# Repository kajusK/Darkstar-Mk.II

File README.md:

DarkStar Mk.II
==============

Small lightweight, water/mud/shock/bomb proof headlamp with bat roasting
light output and Scurion like body for 1/8 of the price. If you are caver,
mine explorer, biker, etc. with hacker soul, this is a way to go!

Features
--------
* Two high power high efficiency XP-L2 LEDs and two low power (e.g. red + UV).
* Up to 869 ANSI lumens (with 80 CRI 4000 K LEDs).
* Anodized aluminium alloy body.
* 3D printed battery box.
* Waterproof up to 2 (tested) meters (IPx8).
* 2 meter drop resistance tested
* Works in wide temperature range - minus 20 °C to plus 60 °C
* Custom high efficiency LED drivers - up to 96 %.
* Up to 2 Amps per LED.
* Runs on single Li-Ion cell, two are recommended for higher run times.
* Thoroughly tested - see [Measurements](./Measurements.md) for more details.
* Simple API for writing custom user modes.
* Temperature and voltage limits to avoid sudden power off or overheating.
* Long run time (over 30 days on lowest mode, over 1,5 hour on full power - for two 3400 mAh cells).
* Low power off current (27 uA), no need to unplug battery after use.
* Easily replaceable LEDs.
* Weights only 277 grams with two 18650 cells.
* Automated light control based on amount of reflected light (EXPERIMENTAL).
* Custom li-ion protection circuit - up to 7 Amps.

Weight
------
* Lamp: 92 g
* Battery box: 50 g
* 2x18650 battery pack: 97 g
* Head strap: 38 g

HowTo
=====
Directories
-----------
* **avr** Source code and hex files for AVR
* **pcb** circuit diagrams, PCBs, gerber files and BOM for electrical parts
* **mechanical** Mechanical BOM, drawings, STLs

Electronics
-----------
The LED drivers were custom designed from elementary components, no integrated
LED solution was used. It's based on hystersis driven buck converter with current
feedback.

The current is sensed by 0,056 ohm resistor, voltage across this resistor is
amplified by opamp and fed to the comparator. The comparator is a brain of the
driver. When the measured voltage is higher than reference voltage generated by
MCU, comparator turns the MOSFET off, current drops below hystersis, MOSFET is turned on
and the cycle repeats. Nothing fancy, but quite simple and cheap.
Only few parts are required and measured efficiency is reaching 96 %. Over 90 \% for
currents over 0,5 A for whole supply voltage range allowed.
Check [Measurement](./Measurements.md) for more details.
The maximal current allowed is 2 Amps. It should be possible to get much higher
currents by choosing better (bigger and more expensice) inductors and transistors.

Disadvantage of such design is a limited lowest possible current, it can't go
below half of the hystersis current. For this reason 10-100 % output is constant
current driven, 0-10 % is controlled by additional PWM.

Software
--------

The brain of the lamp is Attiny 841, it handles key presses, reference voltage
generating, etc. To make it simpler to program I use optiboot arduino compatible
bootloader though there is no arduino code included in the project except
the bootloader itself.

To make it simpler to write your own control modes, most of the code is just a library
controlling the hardware and providing few quite low level functions to user. It
takes care of reading buttons, generating reference voltages for LED drivers, etc.

It also contains automated light control (PI regulator). The light is measured
by phototransistor and the difference between the measured value and value
required is run through the PI regulator. Result is the applied to reference
voltage generator. This feature is quite EXPERIMENTAL and doesn't work
well for caving when the lamps gets covered in mud.

The rest is the user mode. Check [simple mode](./avr/src/modes/simple.c) to see
how simple it can get. All relevant header are included. See [HowTo](./HowTo.md)
for more details on programming and stuff.

The caving mode controls are described in [User guide](./User_guide.md).

Mechanical
----------
The body is machined on a lathe from 6063 aluminium alloy. No fancy expensive
tools except lathe and drill press are required to make the lamp.

Top cover is made from polycarbonate sheet, cable and control rods bushings are
made from brass. The whole thing is sealed with O-rings. See the [BOM](./mechanical/BOM.md)
for more details.

The battery box is designed to be printed on any 3D printer. I would suggest
using ABS and painting the resulting print with ABS juice to get is as
waterproof as possible.

Lenses
------
the wide beam led can be used without lenses, the beam is wide enough for my
needs, for the narrow beam led you can buy any compatible lens that fits inside
the body. I used [17mm 10deg lens]
(http://www.aliexpress.com/item/free-shipping-cree-xp-g-lens-diameter-17mm-smooth-surface-with-stand-condenser-lenses-10-deg/777222733.html)

License
=======

The source code is licenced under [GNU GPL v2](./avr/LICENSE). The mechanical and
electrical design is licensed under [CERN OHL v.1.2](LICENSE).

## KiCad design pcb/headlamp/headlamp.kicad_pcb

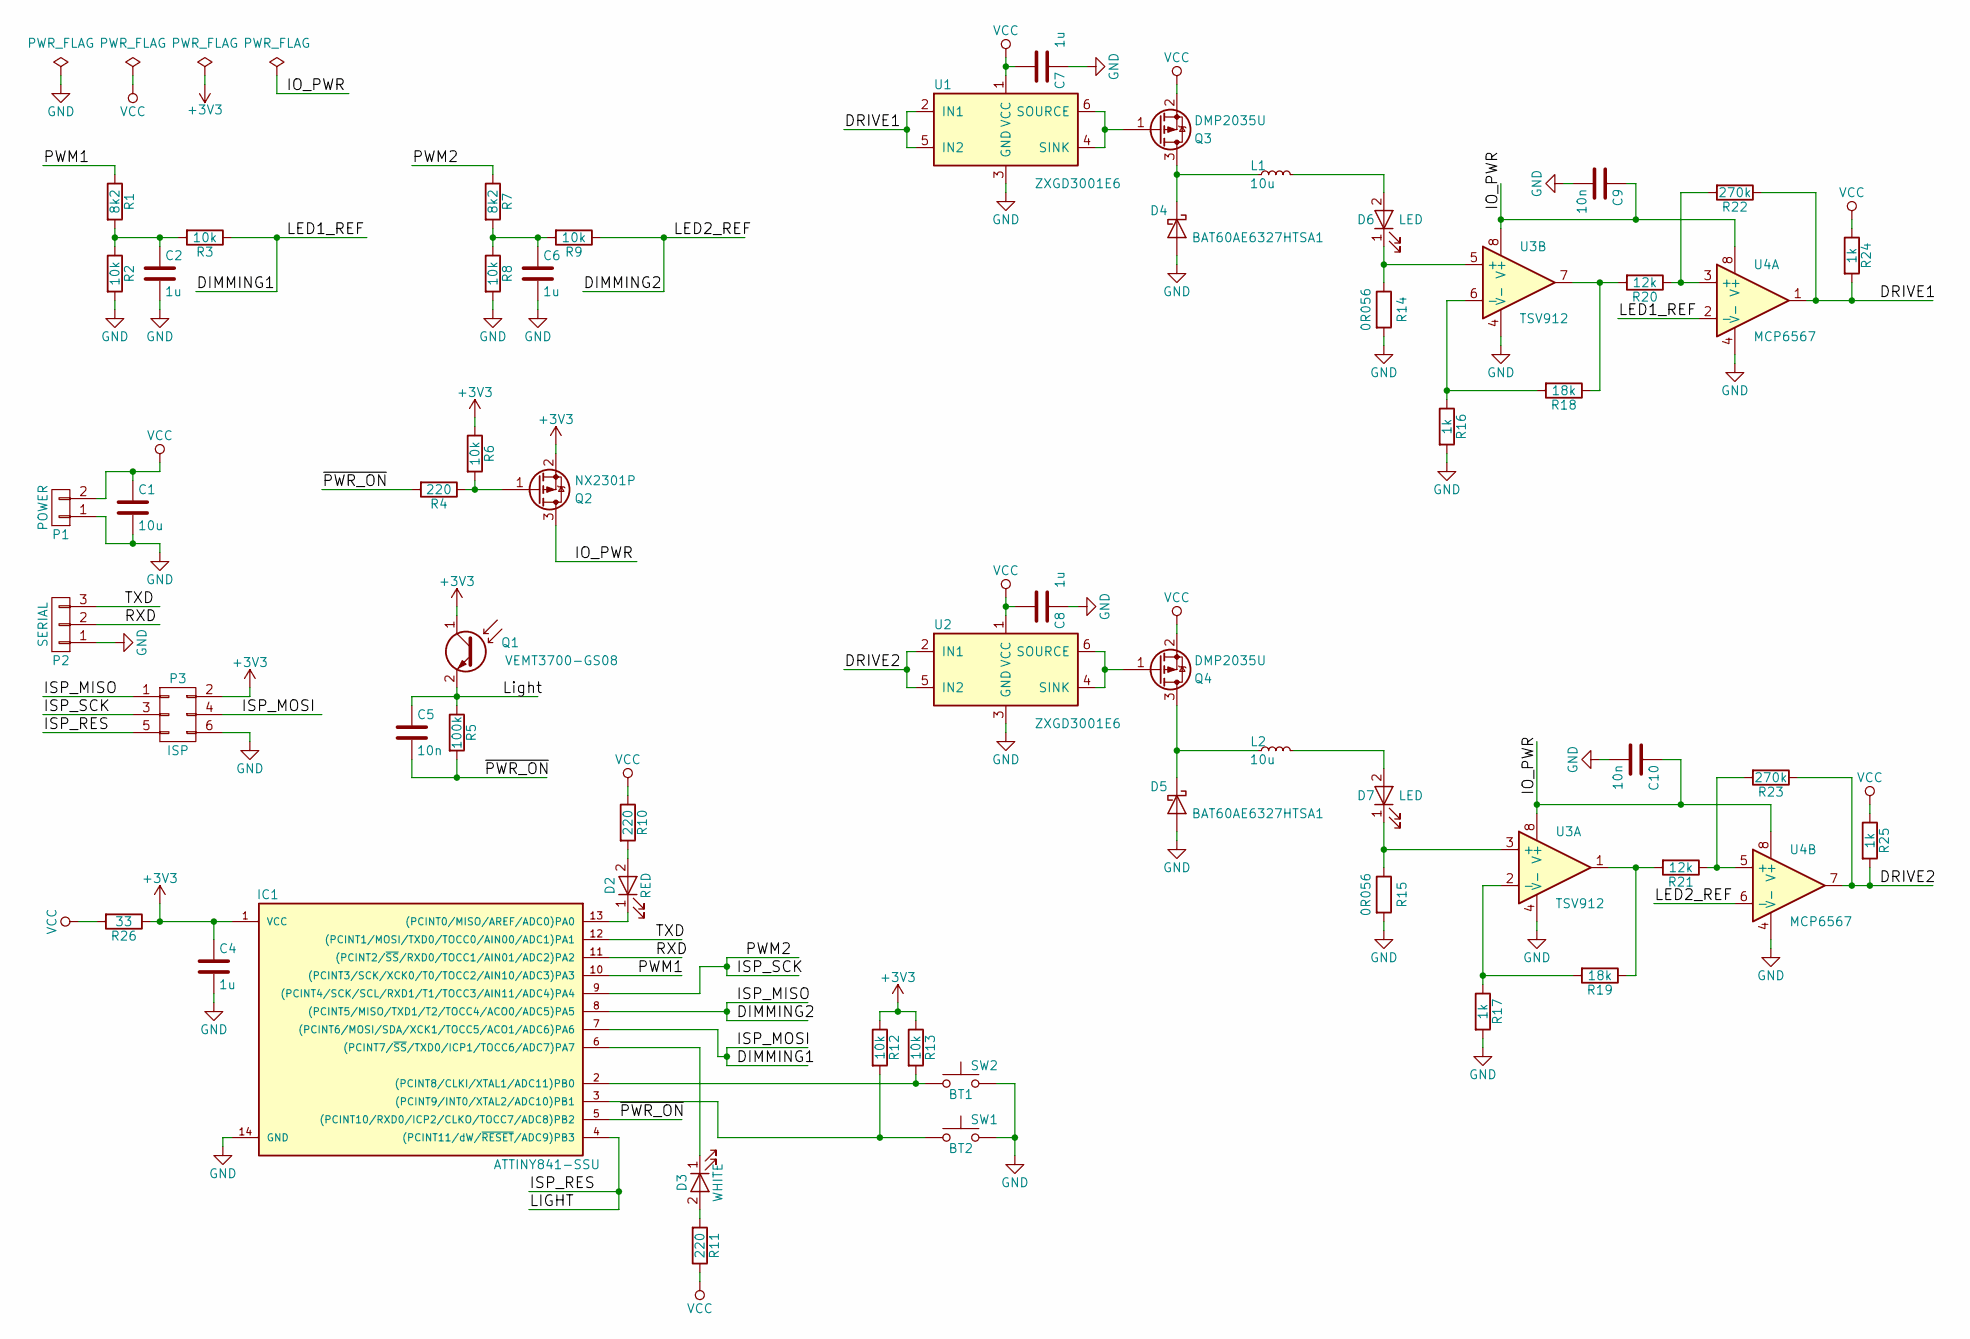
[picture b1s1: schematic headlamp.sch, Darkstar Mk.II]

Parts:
C1: 10u; C_0603
C2, C4, C6, C7, C8: 1u; C_0603
C5, C9, C10: 10n; C_0603
D2: RED; LED_PLCC-2
D3: WHITE; LED_PLCC-2
D4, D5: BAT60AE6327HTSA1; SOD-323
D6, D7: LED; Custom_Conn_2_Big
IC1: ATTINY841-SSU; SOIC-14_3.9x8.7mm_Pitch1.27mm
L1, L2: 10u; Inductor_Bourns-SRU8043
P1: POWER; Custom_Conn_2_Big
P2: SERIAL; GS3
P3: ISP; SOT-23-6
Q1: VEMT3700-GS08; LED_PLCC-2
Q2: NX2301P; SOT-23
Q3, Q4: DMP2035U; SOT-23
R1, R7: 8k2; R_0603
R2, R3, R6, R8, R9, R12, R13: 10k; R_0603
R4, R10, R11: 220; R_0603
R5: 100k; R_0603
R14, R15: 0R056; R_1206
R16, R17, R24, R25: 1k; R_0603
R18, R19: 18k; R_0603
R20, R21: 12k; R_0603
R22, R23: 270k; R_0603
R26: 33; R_0603
SW1: BT2; SW_SPST_FSMSM
SW2: BT1; SW_SPST_FSMSM
U1, U2: ZXGD3001E6; SOT-23-6
U3: TSV912; MSOP-8_3x3mm_Pitch0.65mm
U4: MCP6567; MSOP-8_3x3mm_Pitch0.65mm

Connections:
+3V3: C4.1, IC1.1 (VCC), P3.2, Q1.1 (C), Q2.2 (S), R6.1, R12.1, R13.1, R26.1
/DIMMING1: IC1.7 ((PCINT6/MOSI/SDA/XCK1/TOCC5/ACO1/ADC6)P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), P3.4, R3.1, U4.2 (-)
/DIMMING2: IC1.8 ((PCINT5/MISO/TXD1/T2/TOCC4/ACO0/ADC5)PA5), P3.1, R9.1, U4.6 (-)
/DRIVE1: R22.1, R24.2, U1.2 (IN1), U1.5 (IN2), U4.1
/DRIVE2: R23.1, R25.2, U2.2 (IN1), U2.5 (IN2), U4.7
/IO_PWR: C9.1, C10.1, Q2.3 (D), U3.8 (V+), U4.8 (V+)
/ISP_RES: C5.1, IC1.4 ((PCINT11/dW/~RESET~/ADC9)PB3), P3.5, Q1.2 (E), R5.1
/ISP_SCK: IC1.9 ((PCINT4/SCK/SCL/RXD1/T1/TOCC3/AIN11/ADC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), P3.3, R7.1
/PWM1: IC1.10 ((PCINT3/SCK/XCK0/T0/TOCC2/AIN10/ADC3)PA3), R1.1
/RXD: IC1.11 ((PCINT2/~SS~/RXD0/TOCC1/AIN01/ADC2)PA2), P2.2
/TXD: IC1.12 ((PCINT1/MOSI/TXD0/TOCC0/AIN00/ADC1)PA1), P2.3
/~PWR_ON: C5.2, IC1.5 ((PCINT10/RXD0/ICP2/CLKO/TOCC7/ADC8)PB2), R4.2, R5.2
GND: C1.2, C2.2, C4.2, C6.2, C7.1, C8.1, C9.2, C10.2, D4.2 (A), D5.2 (A), IC1.14 (GND), P1.1, P2.1, P3.6, R2.2, R8.2, R14.2, R15.2, R16.2, R17.2, SW1.2, SW2.2, U1.3 (GND), U2.3 (GND), U3.4 (V-), U4.4 (V-)
unnamed: C2.1, R1.2, R2.1, R3.2
unnamed: C6.1, R7.2, R8.1, R9.2
unnamed: D2.1 (K), IC1.13 ((PCINT0/MISO/AREF/ADC0)PA0)
unnamed: D2.2 (A), R10.2
unnamed: D3.1 (K), IC1.6 ((PCINT7/~SS~/TXD0/ICP1/TOCC6/ADC7)PA7)
unnamed: D3.2 (A), R11.2
unnamed: D4.1 (K), L1.1, Q3.3 (D)
unnamed: D5.1 (K), L2.1, Q4.3 (D)
unnamed: D6.1 (K), R14.1, U3.5 (+)
unnamed: D6.2 (A), L1.2
unnamed: D7.1 (K), R15.1, U3.3 (+)
unnamed: D7.2 (A), L2.2
unnamed: IC1.2 ((PCINT8/CLKI/XTAL1/ADC11)PB0), R13.2, SW2.1
unnamed: IC1.3 ((PCINT9/INT0/XTAL2/ADC10)PB1), R12.2, SW1.1
unnamed: Q2.1 (G), R4.1, R6.2
unnamed: Q3.1 (G), U1.4 (SINK), U1.6 (SOURCE)
unnamed: Q4.1 (G), U2.4 (SINK), U2.6 (SOURCE)
unnamed: R16.1, R18.2, U3.6 (-)
unnamed: R17.1, R19.2, U3.2 (-)
unnamed: R18.1, R20.2, U3.7
unnamed: R19.1, R21.2, U3.1
unnamed: R20.1, R22.2, U4.3 (+)
unnamed: R21.1, R23.2, U4.5 (+)
VCC: C1.1, C7.2, C8.2, P1.2, Q3.2 (S), Q4.2 (S), R10.1, R11.1, R24.1, R25.1, R26.2, U1.1 (VCC), U2.1 (VCC)

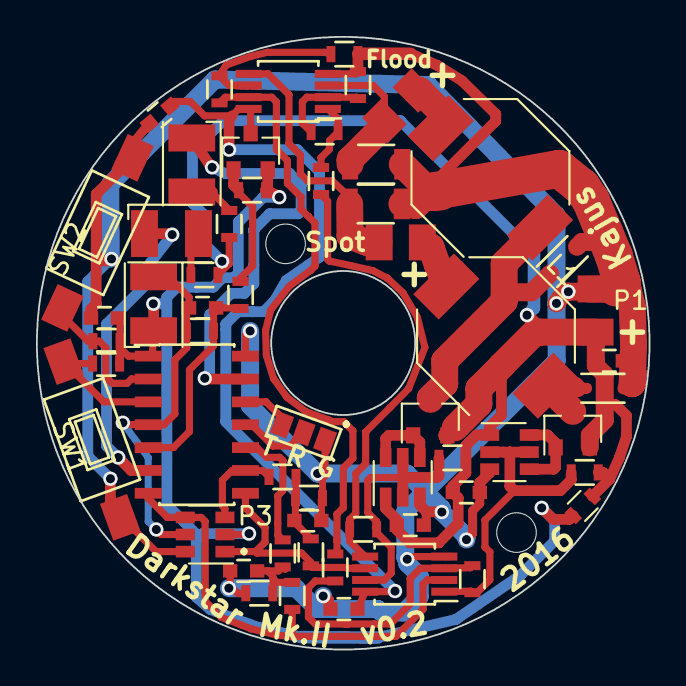
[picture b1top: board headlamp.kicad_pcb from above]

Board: 2 copper layers, 34.0 x 34.0 mm, 57 parts (0 on the bottom side), 37 nets.

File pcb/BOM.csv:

Reference, Value, Footprint,URL
C1,10u,Capacitors_SMD:C_0603,
C10,10n,Capacitors_SMD:C_0603,
C2,1u,Capacitors_SMD:C_0603,
C4,1u,Capacitors_SMD:C_0603,
C5,10n,Capacitors_SMD:C_0603,
C6,1u,Capacitors_SMD:C_0603,
C7,1u,Capacitors_SMD:C_0603,
C8,1u,Capacitors_SMD:C_0603,
C9,10n,Capacitors_SMD:C_0603,
D2,RED,LEDs:LED_PLCC-2,http://cz.farnell.com/osram/lr-t67f-u1aa-1/led-smd-plcc2-red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
D3,WHITE,LEDs:LED_PLCC-2,http://cz.farnell.com/broadcom-limited/asmt-uwb1-nx3e2/led-s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
D4,BAT60AE6327HTSA1,Diodes_SMD:SOD-323,http://cz.farnell.com/infineon/bat-60a-e6327/rectifier-schot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
D5,BAT60AE6327HTSA1,Diodes_SMD:SOD-323,http://cz.farnell.com/infineon/bat-60a-e6327/rectifier-schot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
D6,CREE XP-L2,,http://cz.mouser.com/ProductDetail/Cree-Inc/XPLBWT-00-0000-0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
D7,CREE XP-L2,,http://cz.mouser.com/ProductDetail/Cree-Inc/XPLBWT-00-0000-0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
IC1,ATTINY841-SSU,Housings_SOIC:SOIC-14_3.9x8.7mm_Pitch1.27mm,http://cz.farnell.com/atmel/attiny841-ssur/mcu-8bit-attiny-1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
L1,10u,Inductors:Inductor_Bourns-SRU8043,http://cz.farnell.com/bourns/sru8043-100y/choke-power-shield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
L2,10u,Inductors:Inductor_Bourns-SRU8043,http://cz.farnell.com/bourns/sru8043-100y/choke-power-shield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
Q1,VEMT3700-GS08,LEDs:LED_PLCC-2,http://cz.farnell.com/vishay/vemt3700-gs08/photo-transistor-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
Q2,NX2301P,TO_SOT_Packages_SMD:SOT-23,http://cz.farnell.com/nxp/nx2301p/mosfet-p-ch-20v-2a-sot23/d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
Q3,DMP2035U,TO_SOT_Packages_SMD:SOT-23,http://cz.farnell.com/diodes-inc/dmp2035u/mosfet-p-ch-esd-20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
Q4,DMP2035U,TO_SOT_Packages_SMD:SOT-23,http://cz.farnell.com/diodes-inc/dmp2035u/mosfet-p-ch-esd-20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
R1,8k2,Resistors_SMD:R_0603,
R10,220R,Resistors_SMD:R_0603,
R11,220R,Resistors_SMD:R_0603,
R12,10k,Resistors_SMD:R_0603,
R13,10k,Resistors_SMD:R_0603,
R14,0R056,Resistors_SMD:R_1206,http://cz.farnell.com/te-connectivity/rlp73n2br056jtd/resist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
R15,0R056,Resistors_SMD:R_1206,http://cz.farnell.com/te-connectivity/rlp73n2br056jtd/resist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
R16,1k,Resistors_SMD:R_0603,
R17,1k,Resistors_SMD:R_0603,
R18,18k,Resistors_SMD:R_0603,
R19,18k,Resistors_SMD:R_0603,
R2,10k,Resistors_SMD:R_0603,
R20,12k,Resistors_SMD:R_0603,
R21,12k,Resistors_SMD:R_0603,
R22,270k,Resistors_SMD:R_0603,
R23,270k,Resistors_SMD:R_0603,
R24,1k,Resistors_SMD:R_0603,
R25,1k,Resistors_SMD:R_0603,
R26,33R,Resistors_SMD:R_0603,
R3,10k,Resistors_SMD:R_0603,
R4,220R,Resistors_SMD:R_0603,
R5,10k,Resistors_SMD:R_0603,
R6,10k,Resistors_SMD:R_0603,
R7,8k2,Resistors_SMD:R_0603,
R8,10k,Resistors_SMD:R_0603,
R9,10k,Resistors_SMD:R_0603,
SW1,BT2,Buttons_Switches_SMD:SW_SPST_FSMSM,http://cz.farnell.com/alcoswitch-te-connectivity/1437566-3/p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
SW2,BT1,Buttons_Switches_SMD:SW_SPST_FSMSM,http://cz.farnell.com/alcoswitch-te-connectivity/1437566-3/p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
U1,ZXGD3001E6,TO_SOT_Packages_SMD:SOT-23-6,http://cz.farnell.com/diodes-inc/zxgd3001e6ta/driver-gate-bi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
U2,ZXGD3001E6,TO_SOT_Packages_SMD:SOT-23-6,http://cz.farnell.com/diodes-inc/zxgd3001e6ta/driver-gate-bi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
U3,TSV912,Housings_SSOP:MSOP-8_3x3mm_Pitch0.65mm,http://cz.farnell.com/stmicroelectronics/tsv912aiyst/op-amp-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
U4,MCP6567,Housings_SSOP:MSOP-8_3x3mm_Pitch0.65mm,http://cz.farnell.com/microchip/mcp6567-e-ms/ic-comparator-d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

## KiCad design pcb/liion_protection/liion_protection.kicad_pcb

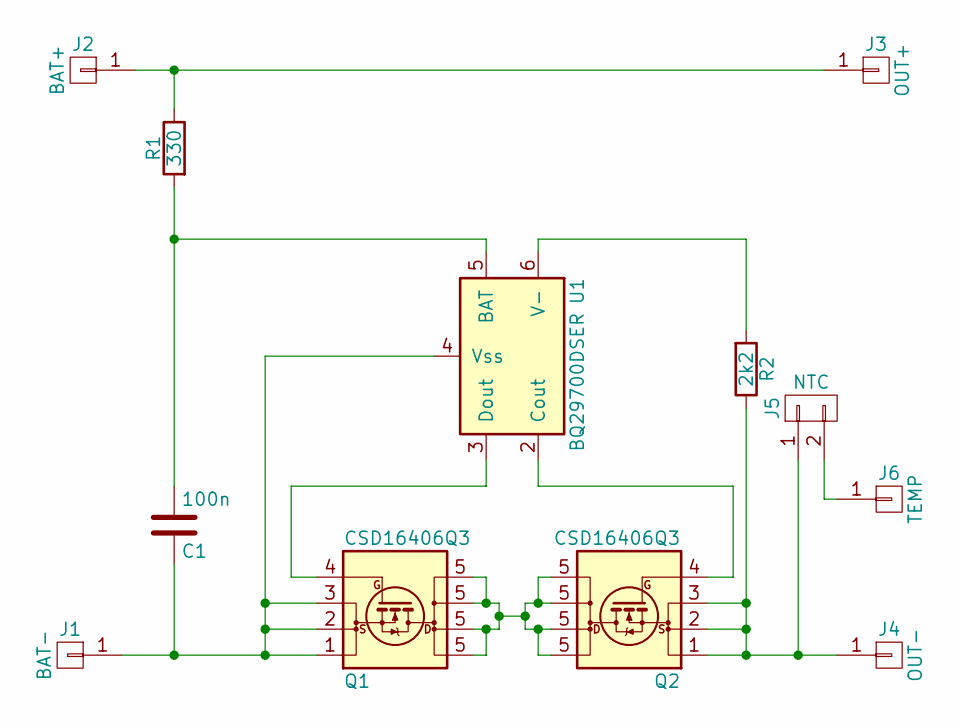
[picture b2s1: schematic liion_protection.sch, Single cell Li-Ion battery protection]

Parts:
C1: 100n; C_0603
J1: BAT-; 1Pin
J2: BAT+; 1Pin
J3: OUT+; 1Pin
J4: OUT-; 1Pin
J5: NTC; GS2
J6: TEMP; 1Pin
Q1, Q2: CSD16406Q3; VSON-8_3.3x3.3mm_Pitch0.65mm_NexFET
R1: 330; R_0603
R2: 2k2; R_0603
U1: BQ29700DSER; WSON6_1.5x1.5mm_Pitch0.5mm

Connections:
unnamed: C1.1, J1.1, Q1.1 (S), Q1.2 (S), Q1.3 (S), U1.4 (Vss)
unnamed: C1.2, R1.2, U1.5 (BAT)
unnamed: J2.1, J3.1, R1.1
unnamed: J4.1, J5.1, Q2.1 (S), Q2.2 (S), Q2.3 (S), R2.1
unnamed: J5.2, J6.1
unnamed: Q1.4 (G), U1.3 (Dout)
unnamed: Q1.5 (D), Q2.5 (D)
unnamed: Q2.4 (G), U1.2 (Cout)
unnamed: R2.2, U1.6 (V-)

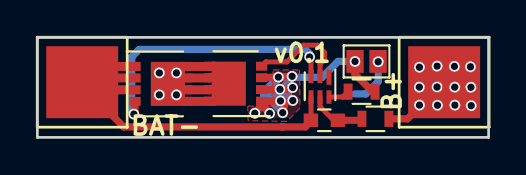
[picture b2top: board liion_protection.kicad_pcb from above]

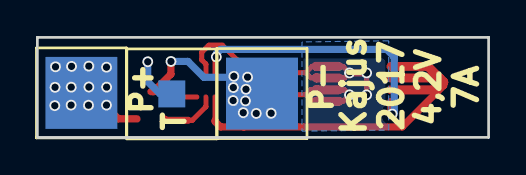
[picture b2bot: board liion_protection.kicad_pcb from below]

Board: 2 copper layers, 25.1 x 5.6 mm, 12 parts (3 on the bottom side), 9 nets.

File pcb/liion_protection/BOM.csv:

Reference, Value, Footprint,URL
Q2,CSD16406Q3,Housings_SON:VSON-8_3.3x3.3mm_Pitch0.65mm_NexFET,http://cz.mouser.com/search/ProductDetail.aspx?R=0virtualkey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
Q1,CSD16406Q3,Housings_SON:VSON-8_3.3x3.3mm_Pitch0.65mm_NexFET,http://cz.mouser.com/search/ProductDetail.aspx?R=0virtualkey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
R2,2k2,Resistors_SMD:R_0603,
R1,330R,Resistors_SMD:R_0603,
C1,100n,Capacitors_SMD:C_0603,
U1,BQ29700DSER,Housings_SON:WSON6_1.5x1.5mm_Pitch0.5mm,http://cz.mouser.com/search/ProductDetail.aspx?R=0virtualkey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

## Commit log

2016-12-04 Rearranged schematics
2016-12-10 Switched to open drain comparator
2016-12-19 First draft of source code
2016-12-20 Added led driver code
2016-12-20 Fixed missing dependency
2016-12-20 Added led pwm dimming
2016-12-20 Fixed typo
2016-12-20 License added
2016-12-20 Simple system timer added
2016-12-20 LEDs moved to hal layer
2016-12-22 Added button handling
2016-12-22 Buttons reading added
2016-12-22 Power off added
2016-12-23 Added forgotten wdt timeout
2016-12-23 PWM dimming must be slower
2016-12-23 Updated function naming
2016-12-23 Events timing added
2016-12-23 Determine amount of ram left
2016-12-28 Board added
2016-12-31 Added gerber files
2016-12-31 Added leds_enabled check function
2016-12-31 Disable leds when going to sleep
2016-12-31 ADC voltage returned in mV
2017-01-01 Added light management
2017-01-01 Main loop added
2017-01-01 Updated makefile to allow compiling different headlamp modes
2017-01-03 Renamed and cleaned sleep function
2017-01-03 Added support for dropin on in supply rail diode protection aka peak detector
2017-01-03 Interrupts setting
2017-01-03 Added power off handling
2017-01-03 Fixed button detection
2017-01-03 added light off function
2017-01-03 Added simple control mode
2017-01-12 Added system_loop function
2017-01-12 removed trailing whitespace
2017-01-12 Added wake up from multiple sources
2017-01-13 Added millis to system library
2017-01-23 Fixed binary safe uart
2017-01-29 Fixed small LEDs connections
2017-01-29 Fixed PWM incorrect register setting
2017-01-29 Fixed typos
2017-01-29 Updated port mapping to match board
2017-01-29 Fixed ram_free declaration
2017-01-29 Fixed =/== error
2017-01-29 Final schematic values, pcb
2017-01-29 Fixed millis timing, attiny not setting overflow flag on match overflow
2017-01-29 Fixed blinking
2017-01-30 Moved get_state to inline
2017-01-30 Turn off pwm output when brightness == 0
2017-01-30 leds enable/disable simplified
2017-01-30 Fixed simple mode light settings
2017-02-03 Fixed uart
2017-02-03 Fixed adc pin setting and conversion result
2017-02-03 ADCL must be read before ADCH
2017-02-03 Updated calculation of vcc for higher accuracy
2017-02-03 Reduced adc frequency for improved accuracy
2017-02-03 Updated defines for adc api
2017-02-03 fixed system voltage reading when diode is used
2017-02-03 Fixed limits clear
2017-02-03 Fixed programming speed
2017-02-03 Updated system constants
2017-02-03 Turn off pwm when battery dead or body overheated
2017-02-11 Added hystersis to limits
2017-02-11 Ignore limits for small leds
2017-02-11 Slowed dimming PWM - the output was not stable over 150Hz
2017-02-16 Updated low voltage levels
2017-03-06 Added user limits
2017-03-06 Hard limits updated
2017-03-09 added option to disable uart
2017-03-09 Added config read/write for storing user data to eeprom
2017-03-09 Added logging wdt resets to eeprom
2017-03-09 Cleaned main
2017-03-09 Added button press detection after powerup
2017-03-09 Fixed initial value of eeprom wdt reset counter
2017-03-09 Caving mode draft
2017-03-09 Fixed hole between short and long press
2017-03-09 Initialize mode in init rather than in variable definition
2017-03-10 Refractored simple mode
2017-03-11 Fixed PWM settings for led
2017-03-11 Updated capacitors values
2017-03-11 Simple mode for hardware testing
2017-03-11 Fixed waking up
2017-03-11 fixed modes switching in simple mode
2017-03-11 fixed level switching
2017-03-17 Fixed button reading on startup
2017-03-17 Minor fixes to caving mode
2017-03-18 Updated phototransistor wiring due to error on board
2017-03-19 Added pid light regulation
2017-03-19 added WDT reset after waking up
2017-03-20 Updated default blink level to reasonable value
2017-03-20 Added config mode
2017-03-20 Removed unnecessary output settings for blinking
2017-03-21 Updated config read/write definition
2017-03-21 Output hex has same name as the mode
2017-03-21 Read temperature and voltage only once per cycle
2017-03-21 Auto mode can't be used together with dimming
2017-03-21 Updated selftest output levels
2017-03-21 Fixed no voltage report on full
2017-03-21 Added user light reading function
2017-03-21 Programming mode fixed
2017-03-21 Updated limits
2017-03-22 Merged reporting and rating voltage levels
2017-03-24 Fixed wdt timeout when writing to eeprom
2017-03-24 Fixed configuration mode
2017-04-09 Fixed PID calculations
2017-04-09 Removed redundant line
2017-04-09 Added start/stop option to pid tuner
2017-04-09 Error when UART_ENABLED not set in pid tuner
2017-04-09 Fixed auto light control ranges
2017-04-09 Added fuse programming to makefile
2017-04-09 Updated Clean in Makefile
2017-04-13 Added additional light step to simple mode
2017-04-15 added one side limits for voltage
2017-04-15 Avoid setting all leds off in programming
2017-04-15 Blink with same led for all actions
2017-04-23 Replaced diode by resistor - was causing rising mcu VCC from spikes on power lines
2017-04-25 Added stls for battery box
2017-04-27 Fixed short blink when going to programming mode
2017-04-27 Added check for empty modes to config loading
2017-04-28 Disabled serial
2017-04-28 Fixed blinking when turning off from dimming mode
2017-04-28 updated ifdef in main
2017-04-28 Added option to disable phototransistor
2017-04-30 Initial documentation
2017-04-30 Disabled eeprom image creation - not used
2017-05-08 Added BOM
2017-05-12 Refractored next level computation
2017-05-12 Updated steps
2017-05-12 Fixed low voltage reporting
2017-05-12 Average system voltage
2017-05-12 Updated battery limiting
2017-05-12 Updated constants
2017-05-12 Initial drawings
2017-05-19 Fixed limits for negative temperature
2017-05-21 Addded images
2017-05-21 Added drawings
2017-05-22 Added liion protection pcb
2017-05-22 Removed panelized headlamp
2017-05-22 Remove voltage spikes building up
2017-05-22 Updated BOM
2017-05-22 Updated docs
2017-05-22 Fixed table
2017-05-22 Added pdf schematics
2017-05-26 Updated automated light control
2017-08-16 Replaced phototransistor by LED
2017-08-16 Refractored battery limits
2017-08-16 Timing updated
2017-09-18 Turn of blinking immediately when powered off
2017-09-18 Fixed flags for programming fuses
2017-09-24 Detect empty eeprom reliably
2017-09-24 Match RED/WHITE led to pcb description
2017-09-24 Make usbtinyisp default programmer
2017-09-24 Fixed central rod dimensions
2017-11-17 Reverting cf8523e112e265d334897d2c1916c9e983e853a5
2017-11-19 Added weight measurements
2017-11-19 Testing heat and impact resistance
2017-12-10 Added better seal to battery box
2017-12-20 Added missing o-ring to BOM
2017-12-21 Moved cutout little higher
2018-01-18 removed unnecessary time_diff
2018-03-19 Fixed hole size
2018-03-28 Fixed hole position
2018-06-24 Removed occasional flashes when changing modes
